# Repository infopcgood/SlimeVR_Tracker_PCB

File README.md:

# SlimeVR_Tracker_PCB
This repository is for my SlimeVR project.

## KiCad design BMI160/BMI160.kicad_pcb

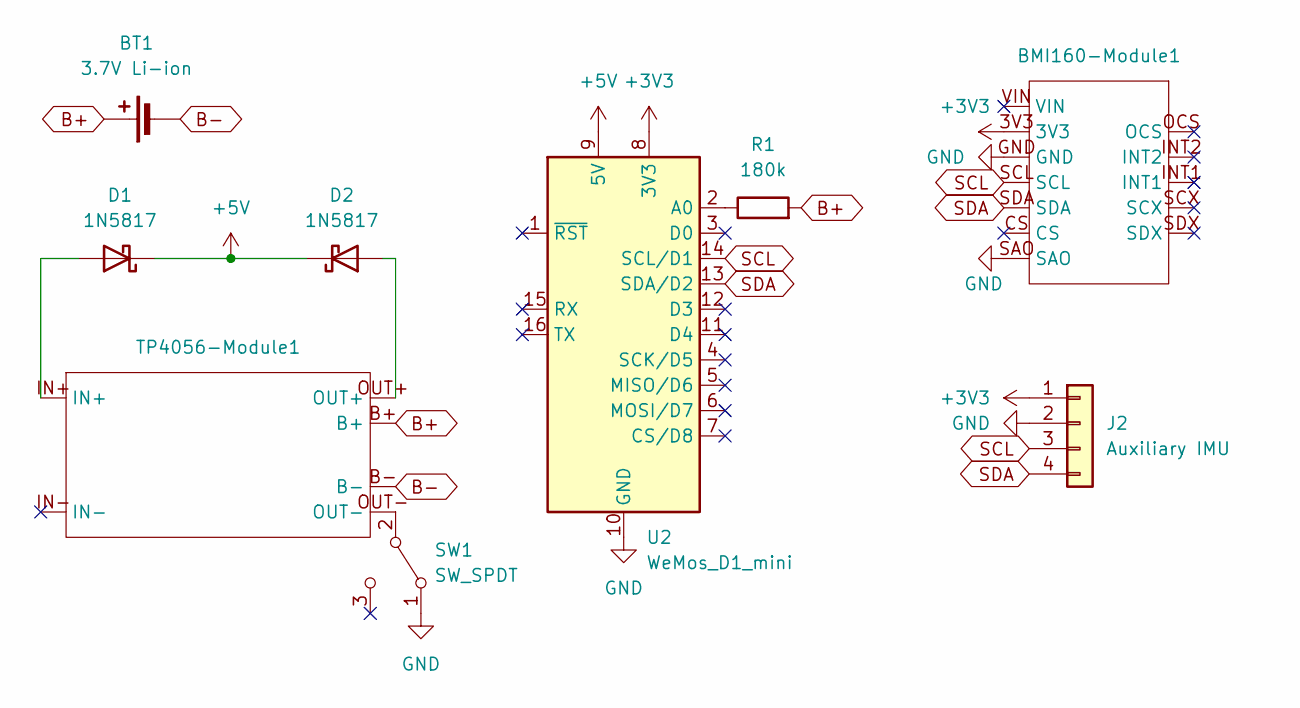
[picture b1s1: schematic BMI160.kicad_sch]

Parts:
BMI160-Module1: BMI160-Module
BT1: 3.7V Li-ion; PinHeader_1x02_P2.54mm_Vertical
D1, D2: 1N5817; D_DO-41_SOD81_P10.16mm_Horizontal
J2: Auxiliary IMU; JST_XH_S4B-XH-A_1x04_P2.50mm_Horizontal
R1: 180k; R_Axial_DIN0207_L6.3mm_D2.5mm_P10.16mm_Horizontal
SW1: SW_SPDT; PinHeader_1x03_P2.54mm_Vertical
TP4056-Module1: TP4056-Module
U2: WeMos_D1_mini; WEMOS_D1_mini_light

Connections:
+3V3: BMI160-Module1.3V3, J2.1, U2.8 (3V3)
+5V: D1.1 (K), D2.1 (K), U2.9 (5V)
B+: BT1.1 (+), R1.2, TP4056-Module1.B+
B-: BT1.2 (-), TP4056-Module1.B-
GND: BMI160-Module1.GND, BMI160-Module1.SAO, J2.2, SW1.1 (A), U2.10 (GND)
unnamed: D1.2 (A), TP4056-Module1.IN+
unnamed: D2.2 (A), TP4056-Module1.OUT+
unnamed: SW1.2 (B), TP4056-Module1.OUT-
unnamed: R1.1, U2.2 (A0)
SCL: BMI160-Module1.SCL, J2.3, U2.14 (SCL/D1)
SDA: BMI160-Module1.SDA, J2.4, U2.13 (SDA/D2)

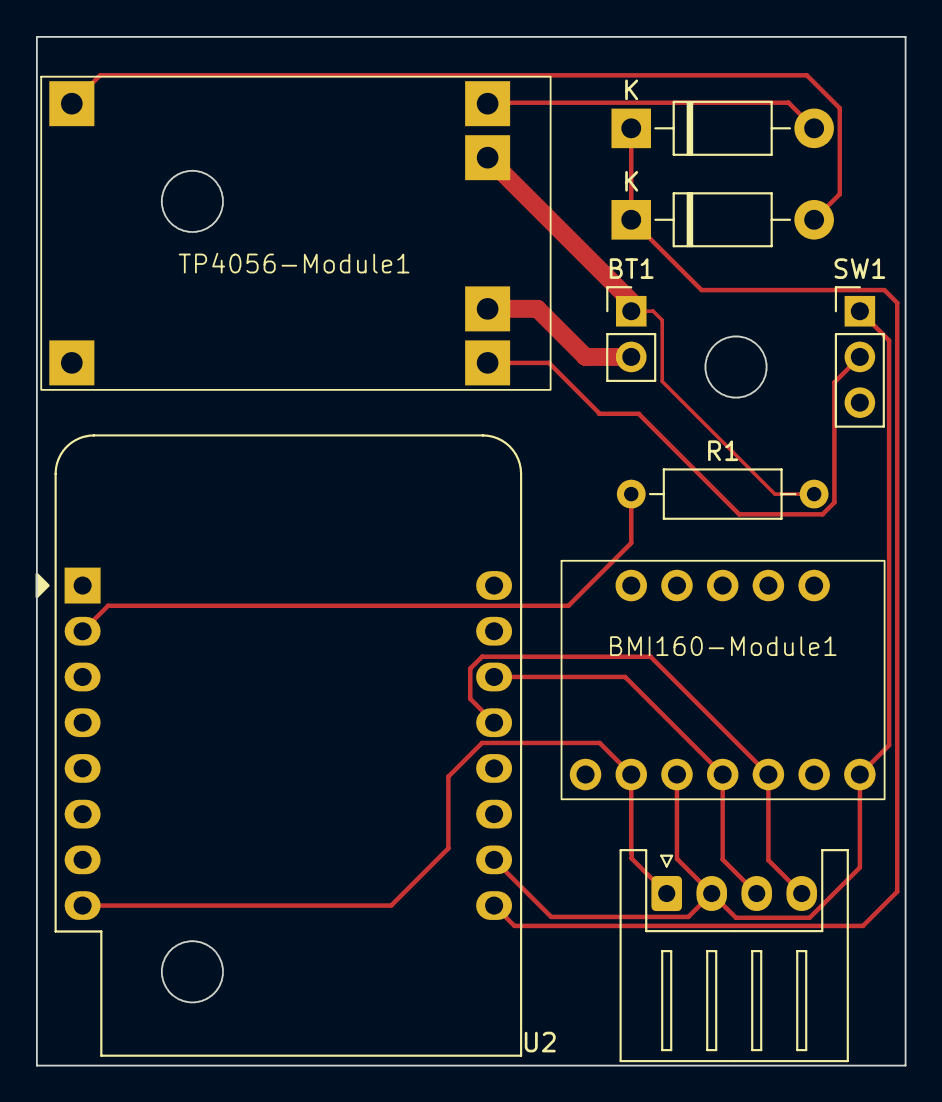
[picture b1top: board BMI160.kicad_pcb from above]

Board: 2 copper layers, 48.3 x 57.2 mm, 9 parts (0 on the bottom side), 11 nets.

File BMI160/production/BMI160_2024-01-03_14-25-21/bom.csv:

Designator,Footprint,Quantity,Value,LCSC Part #
BMI160-Module1,BMI160-Module,1,~,
BT1,PinHeader_1x02_P2.54mm_Vertical,1,3.7V Li-ion,
"D1, D2",D_DO-41_SOD81_P10.16mm_Horizontal,2,1N5817,
J2,JST_XH_S4B-XH-A_1x04_P2.50mm_Horizontal,1,Auxiliary IMU,
R1,R_Axial_DIN0207_L6.3mm_D2.5mm_P10.16mm_Horizontal,1,180k,
SW1,PinHeader_1x03_P2.54mm_Vertical,1,SW_SPDT,
TP4056-Module1,TP4056-Module,1,~,
U2,WEMOS_D1_mini_light,1,WeMos_D1_mini,

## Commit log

2024-03-04 Initial commit with BMI160
2024-03-04 Add README.md
